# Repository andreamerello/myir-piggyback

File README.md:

Piggyback board for Z-Turn Myir
===============================

In this repo you can find the (simple) schematic, the PCB design, and gerber files, for a breakout board for the Z-Turn Myir board.

The board simply routes all the signals from Z-Turn expansion connector to two regular 2.54 (like RPi/Arduino) pinstrips.

The design is made with KiCad.

*WARNING*: I've not build it yet. Not tested...

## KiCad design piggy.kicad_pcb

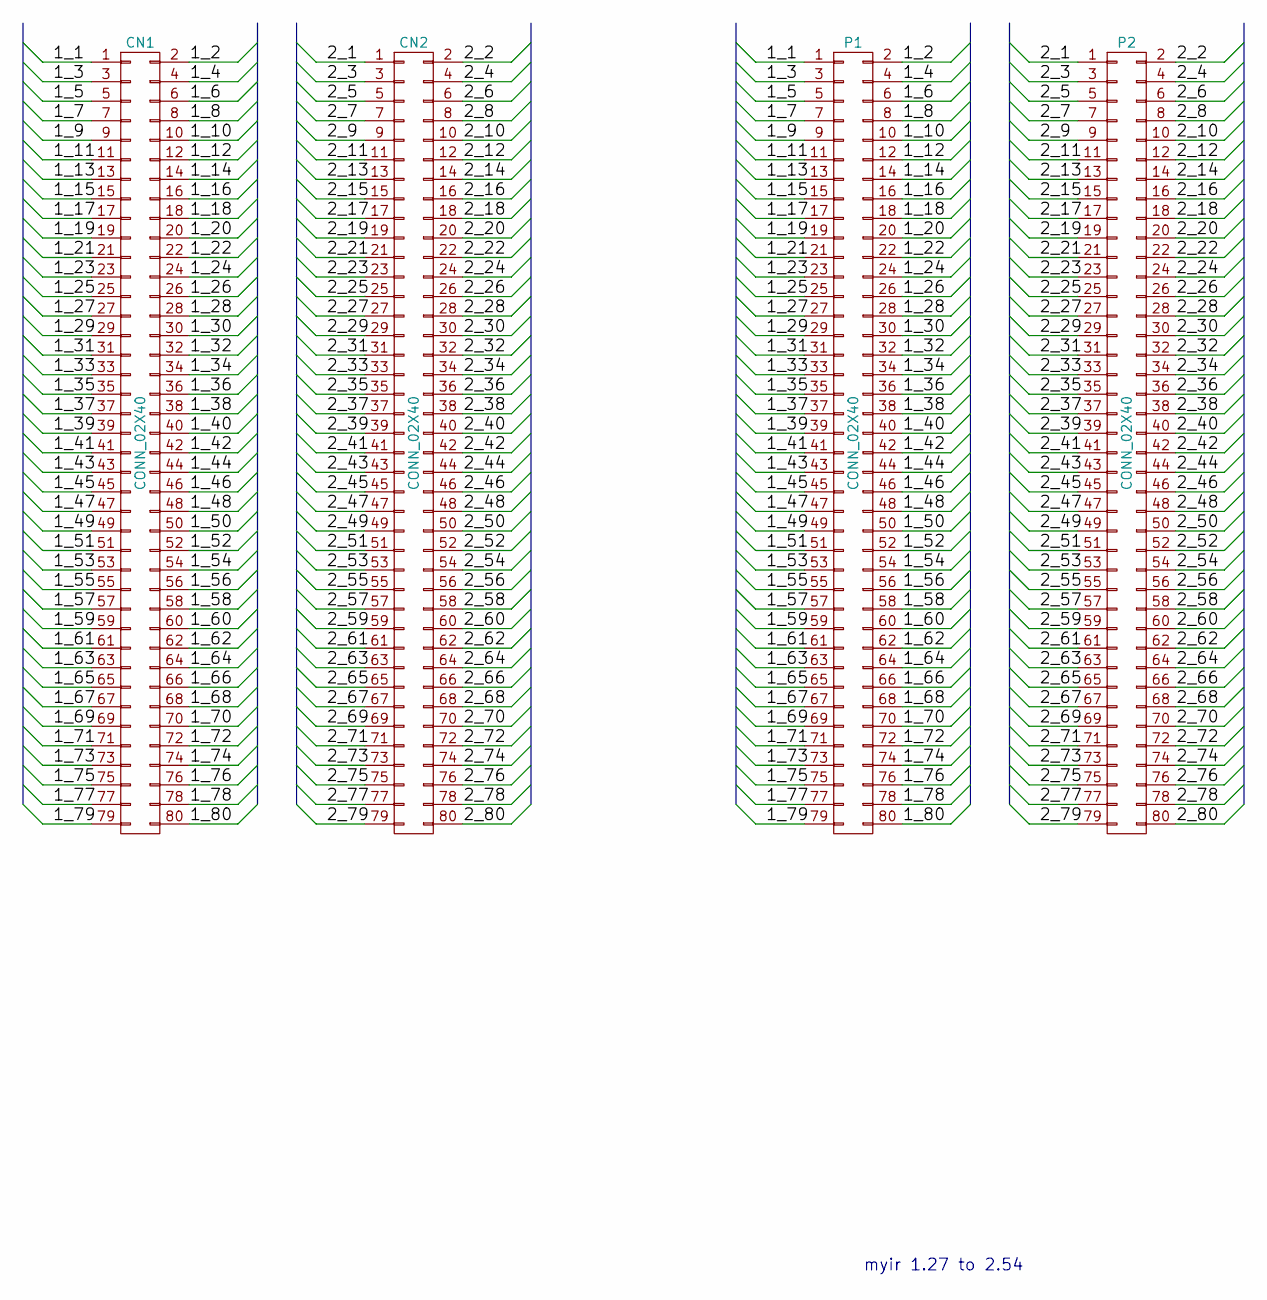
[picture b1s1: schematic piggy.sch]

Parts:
CN1, CN2: CONN_02X40; header-1.27-2x40
P1, P2: CONN_02X40; Pin_Header_Straight_2x40

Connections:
/1_1: CN1.1, P1.1
/1_2: CN1.2, P1.2
/1_3: CN1.3, P1.3
/1_4: CN1.4, P1.4
/1_5: CN1.5, P1.5
/1_6: CN1.6, P1.6
/1_7: CN1.7, P1.7
/1_8: CN1.8, P1.8
/1_9: CN1.9, P1.9
/1_10: CN1.10, P1.10
/1_11: CN1.11, P1.11
/1_12: CN1.12, P1.12
/1_13: CN1.13, P1.13
/1_14: CN1.14, P1.14
/1_15: CN1.15, P1.15
/1_16: CN1.16, P1.16
/1_17: CN1.17, P1.17
/1_18: CN1.18, P1.18
/1_19: CN1.19, P1.19
/1_20: CN1.20, P1.20
/1_21: CN1.21, P1.21
/1_22: CN1.22, P1.22
/1_23: CN1.23, P1.23
/1_24: CN1.24, P1.24
/1_25: CN1.25, P1.25
/1_26: CN1.26, P1.26
/1_27: CN1.27, P1.27
/1_28: CN1.28, P1.28
/1_29: CN1.29, P1.29
/1_30: CN1.30, P1.30
/1_31: CN1.31, P1.31
/1_32: CN1.32, P1.32
/1_33: CN1.33, P1.33
/1_34: CN1.34, P1.34
/1_35: CN1.35, P1.35
/1_36: CN1.36, P1.36
/1_37: CN1.37, P1.37
/1_38: CN1.38, P1.38
/1_39: CN1.39, P1.39
/1_40: CN1.40, P1.40
/1_41: CN1.41, P1.41
/1_42: CN1.42, P1.42
/1_43: CN1.43, P1.43
/1_44: CN1.44, P1.44
/1_45: CN1.45, P1.45
/1_46: CN1.46, P1.46
/1_47: CN1.47, P1.47
/1_48: CN1.48, P1.48
/1_49: CN1.49, P1.49
/1_50: CN1.50, P1.50
/1_51: CN1.51, P1.51
/1_52: CN1.52, P1.52
/1_53: CN1.53, P1.53
/1_54: CN1.54, P1.54
/1_55: CN1.55, P1.55
/1_56: CN1.56, P1.56
/1_57: CN1.57, P1.57
/1_58: CN1.58, P1.58
/1_59: CN1.59, P1.59
/1_60: CN1.60, P1.60
/1_61: CN1.61, P1.61
/1_62: CN1.62, P1.62
/1_63: CN1.63, P1.63
/1_64: CN1.64, P1.64
/1_65: CN1.65, P1.65
/1_66: CN1.66, P1.66
/1_67: CN1.67, P1.67
/1_68: CN1.68, P1.68
/1_69: CN1.69, P1.69
/1_70: CN1.70, P1.70
/1_71: CN1.71, P1.71
/1_72: CN1.72, P1.72
/1_73: CN1.73, P1.73
/1_74: CN1.74, P1.74
/1_75: CN1.75, P1.75
/1_76: CN1.76, P1.76
/1_77: CN1.77, P1.77
/1_78: CN1.78, P1.78
/1_79: CN1.79, P1.79
/1_80: CN1.80, P1.80
/2_1: CN2.1, P2.1
/2_2: CN2.2, P2.2
/2_3: CN2.3, P2.3
/2_4: CN2.4, P2.4
/2_5: CN2.5, P2.5
/2_6: CN2.6, P2.6
/2_7: CN2.7, P2.7
/2_8: CN2.8, P2.8
/2_9: CN2.9, P2.9
/2_10: CN2.10, P2.10
/2_11: CN2.11, P2.11
/2_12: CN2.12, P2.12
/2_13: CN2.13, P2.13
/2_14: CN2.14, P2.14
/2_15: CN2.15, P2.15
/2_16: CN2.16, P2.16
/2_17: CN2.17, P2.17
/2_18: CN2.18, P2.18
/2_19: CN2.19, P2.19
/2_20: CN2.20, P2.20
/2_21: CN2.21, P2.21
/2_22: CN2.22, P2.22
/2_23: CN2.23, P2.23
/2_24: CN2.24, P2.24
/2_25: CN2.25, P2.25
/2_26: CN2.26, P2.26
/2_27: CN2.27, P2.27
/2_28: CN2.28, P2.28
/2_29: CN2.29, P2.29
/2_30: CN2.30, P2.30
/2_31: CN2.31, P2.31
/2_32: CN2.32, P2.32
/2_33: CN2.33, P2.33
/2_34: CN2.34, P2.34
/2_35: CN2.35, P2.35
/2_36: CN2.36, P2.36
/2_37: CN2.37, P2.37
/2_38: CN2.38, P2.38
/2_39: CN2.39, P2.39
/2_40: CN2.40, P2.40
/2_41: CN2.41, P2.41
/2_42: CN2.42, P2.42
/2_43: CN2.43, P2.43
/2_44: CN2.44, P2.44
/2_45: CN2.45, P2.45
/2_46: CN2.46, P2.46
/2_47: CN2.47, P2.47
/2_48: CN2.48, P2.48
/2_49: CN2.49, P2.49
/2_50: CN2.50, P2.50
/2_51: CN2.51, P2.51
/2_52: CN2.52, P2.52
/2_53: CN2.53, P2.53
/2_54: CN2.54, P2.54
/2_55: CN2.55, P2.55
/2_56: CN2.56, P2.56
/2_57: CN2.57, P2.57
/2_58: CN2.58, P2.58
/2_59: CN2.59, P2.59
/2_60: CN2.60, P2.60
/2_61: CN2.61, P2.61
/2_62: CN2.62, P2.62
/2_63: CN2.63, P2.63
/2_64: CN2.64, P2.64
/2_65: CN2.65, P2.65
/2_66: CN2.66, P2.66
/2_67: CN2.67, P2.67
/2_68: CN2.68, P2.68
/2_69: CN2.69, P2.69
/2_70: CN2.70, P2.70
/2_71: CN2.71, P2.71
/2_72: CN2.72, P2.72
/2_73: CN2.73, P2.73
/2_74: CN2.74, P2.74
/2_75: CN2.75, P2.75
/2_76: CN2.76, P2.76
/2_77: CN2.77, P2.77
/2_78: CN2.78, P2.78
/2_79: CN2.79, P2.79
/2_80: CN2.80, P2.80

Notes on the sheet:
myir 1.27 to 2.54

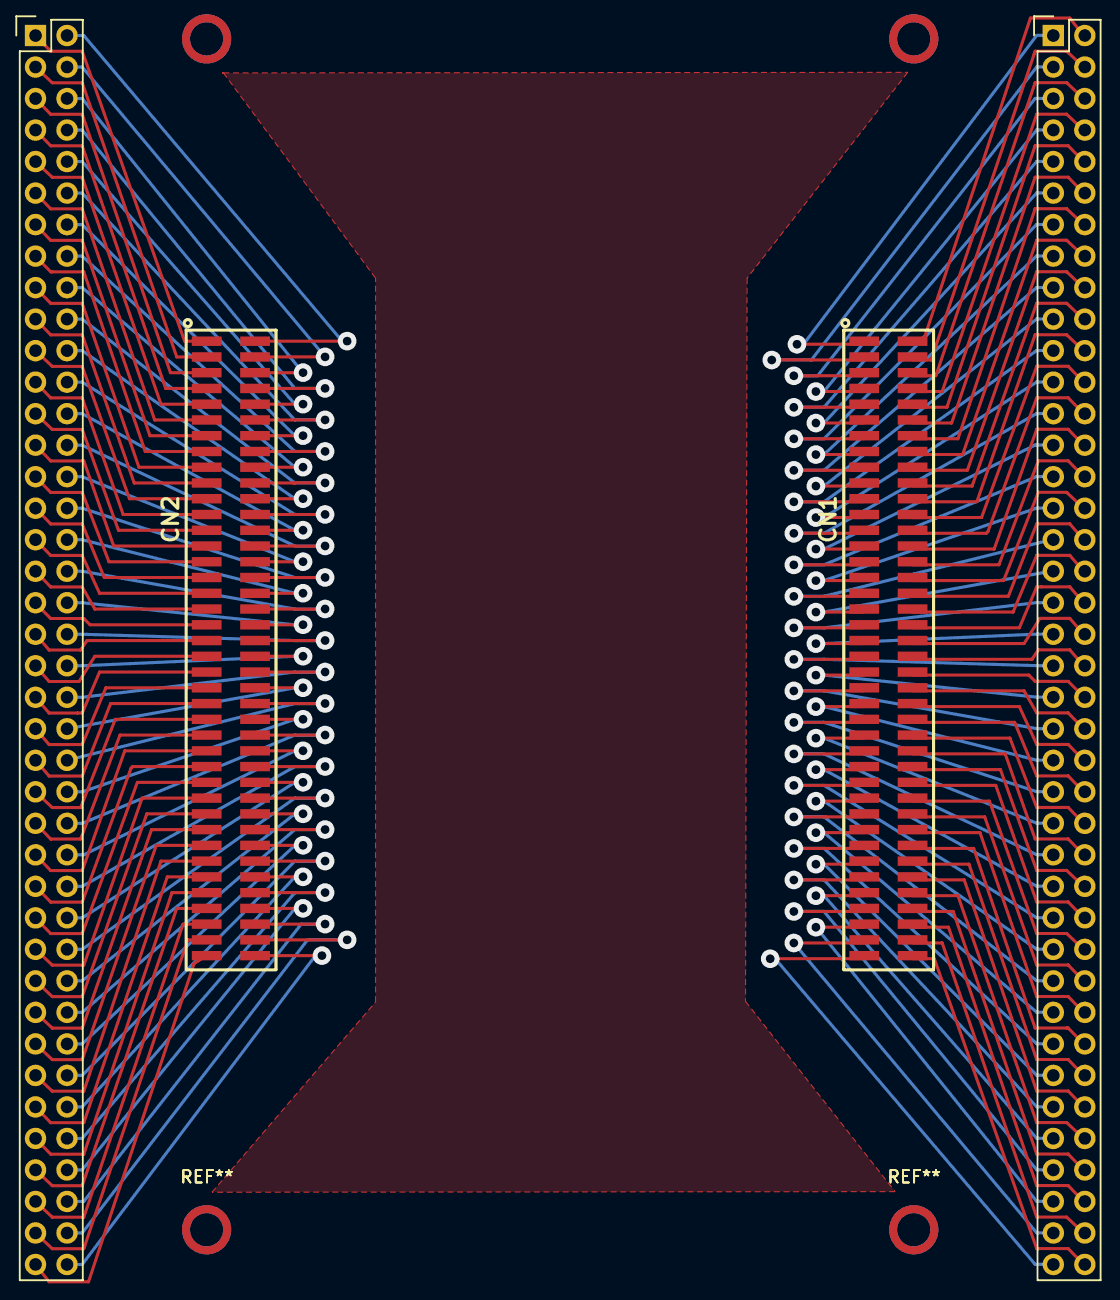
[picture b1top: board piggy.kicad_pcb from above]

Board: 2 copper layers, 4 parts (0 on the bottom side), 160 nets.

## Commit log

2016-06-09 commit first version
2016-06-09 Add basic doc
